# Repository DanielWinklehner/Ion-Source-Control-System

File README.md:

# Ion Source Control System

## Arduino Error Codes
'ERR0' => Undefined error (does not fall into any of the other 9 categories).
'ERR1' => Asking a precision that's too high (> 6).
'ERR2' => Asking for something that would return more than 128 bytes.
'ERR3' => Invalid number of channels.
'ERR4' => Querying for a channel that does not exist.
'ERR5' => ...
'ERR6' => ...
'ERR7' => ...
...

## Libraries to Install

## Killing the server.

```bash
ps aux | grep RasPiServer.py | grep -v grep | awk '{print $2}' | xargs kill -9 ; python RasPiServer.py 
```

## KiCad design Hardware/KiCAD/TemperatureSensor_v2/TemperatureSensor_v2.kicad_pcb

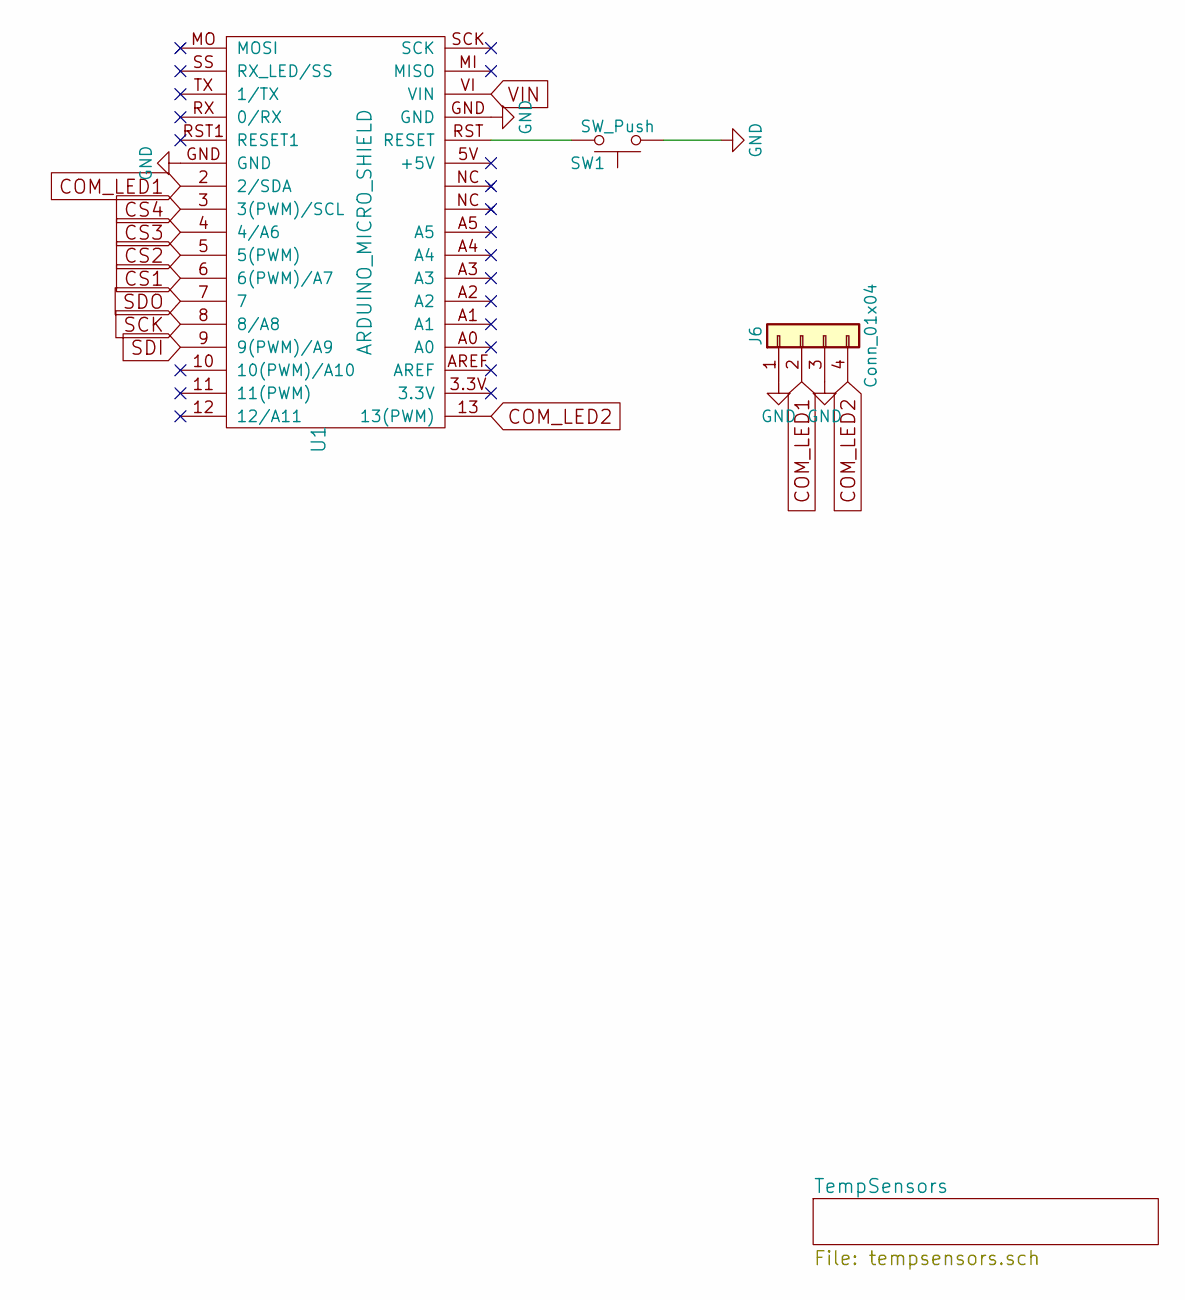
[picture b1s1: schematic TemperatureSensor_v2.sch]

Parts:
J6: Conn_01x04; TerminalBlock_Phoenix_MPT-2.54mm_4pol
SW1: SW_Push; SW_Tactile_SPST_Angled_PTS645Vx39-2LFS
U1: ARDUINO_MICRO_SHIELD; ARDUINO_MICRO_SHIELD1

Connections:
COM_LED1: J6.2, U1.2 (2/SDA)
COM_LED2: J6.4, U1.13 (13(PWM))
CS1: U1.6 (6(PWM)/A7); also elsewhere on the board
CS2: U1.5 (5(PWM)); also elsewhere on the board
CS3: U1.4 (4/A6); also elsewhere on the board
CS4: U1.3 (3(PWM)/SCL); also elsewhere on the board
GND: J6.1, J6.3, SW1.1, U1.GND; also elsewhere on the board
unnamed: SW1.2, U1.RST (RESET)
SCK: U1.8 (8/A8); also elsewhere on the board
SDI: U1.9 (9(PWM)/A9); also elsewhere on the board
SDO: U1.7; also elsewhere on the board
VIN: U1.VI (VIN); also elsewhere on the board

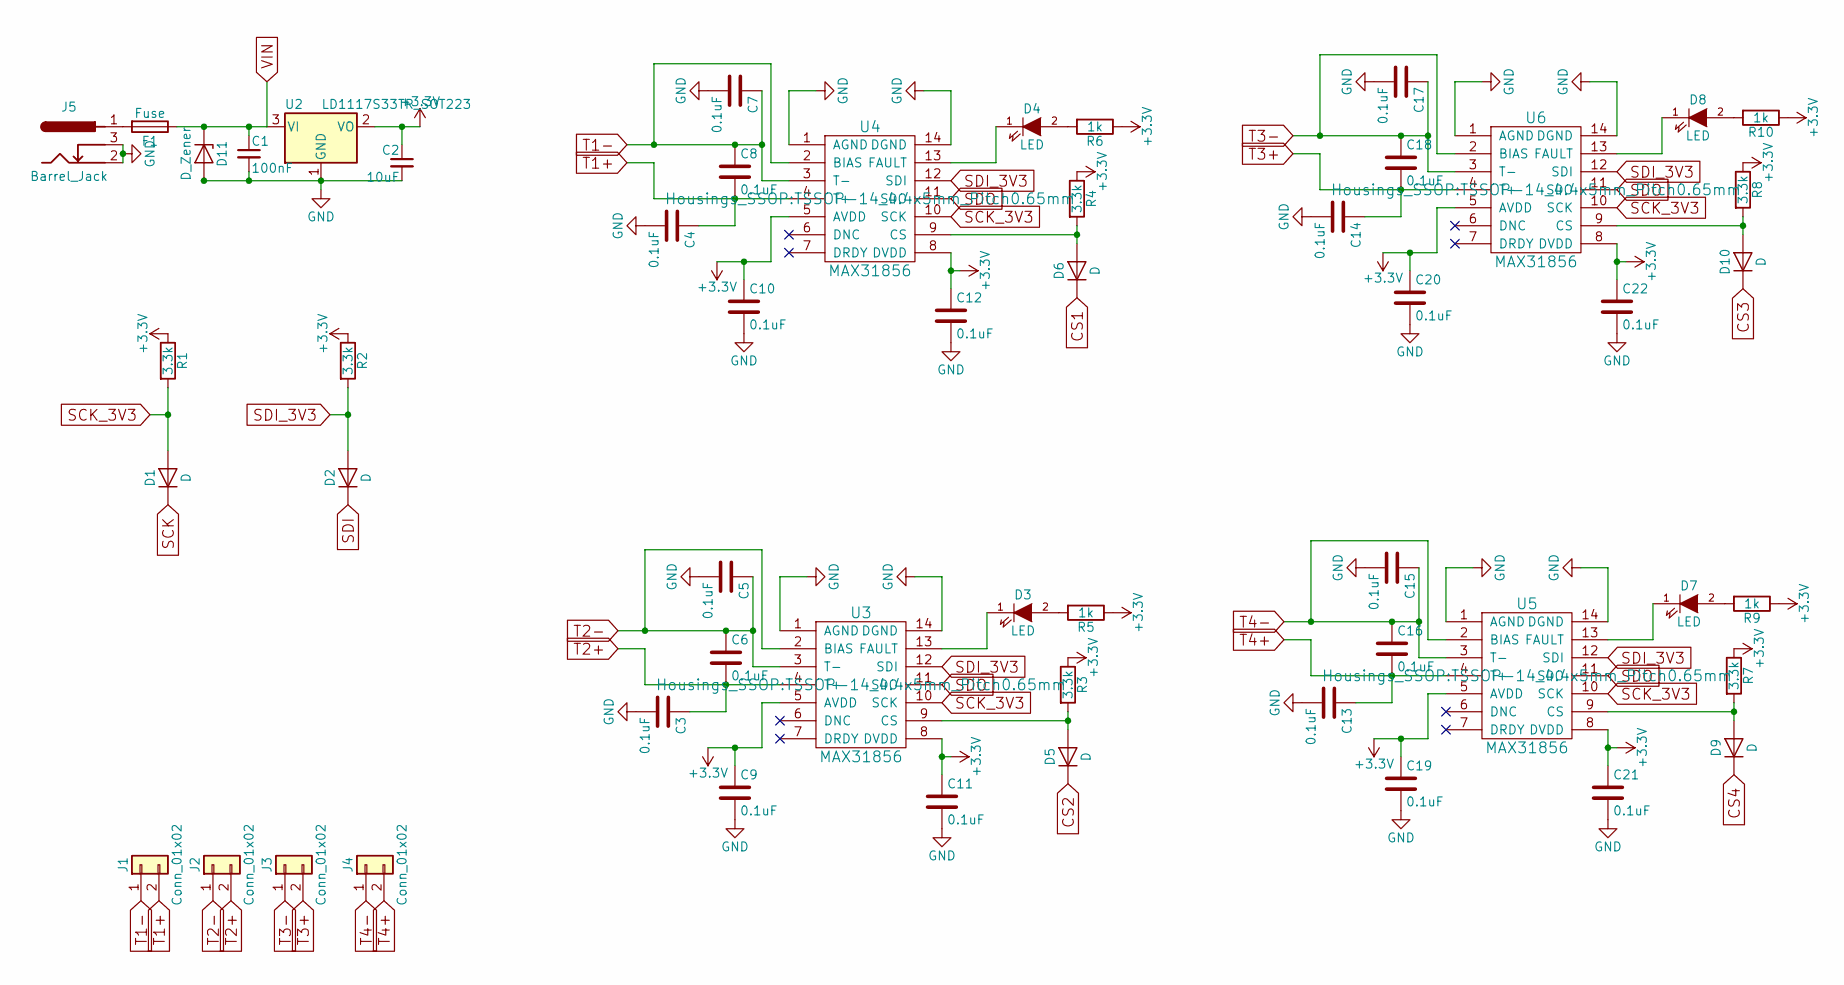
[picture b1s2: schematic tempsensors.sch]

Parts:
C1: 100nF; C_0805
C2: 10uF; C_0805
C3, C4, C5, C6, C7, C8, C9, C10, C11, C12, C13, C14, C15, C16, C17, C18, C19, C20, C21, C22: 0.1uF; C_0805
D1, D2, D5, D6, D9, D10: D; D_SOD-323
D3, D4, D7, D8: LED; LED_0603
D11: D_Zener; D_0805
F1: Fuse; Fuseholder5x20_horiz_open_inline_Type-I
J1, J2, J3, J4: Conn_01x02; Thermocouple_Pins
J5: Barrel_Jack; BARREL_JACK
R1, R2, R3, R4, R7, R8: 3.3k; R_0603
R5, R6, R9, R10: 1k; R_0603
U2: LD1117S33TR_SOT223; TO-220-3_Vertical
U3, U4, U5, U6: MAX31856; TSSOP-14_4.4x5mm_Pitch0.65mm

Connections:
+3V3: C2.1, C9.1, C10.1, C11.1, C12.1, C19.1, C20.1, C21.1, C22.1, R1.1, R2.1, R3.1, R4.1, R5.1, R6.1, R7.1, R8.1, R9.1, R10.1, U2.2 (VO), U3.5 (AVDD), U3.8 (DVDD), U4.5 (AVDD), U4.8 (DVDD), U5.5 (AVDD), U5.8 (DVDD), U6.5 (AVDD), U6.8 (DVDD)
CS1: D6.1 (K); also elsewhere on the board
CS2: D5.1 (K); also elsewhere on the board
CS3: D10.1 (K); also elsewhere on the board
CS4: D9.1 (K); also elsewhere on the board
GND: C1.2, C2.2, C3.2, C4.2, C5.2, C7.2, C9.2, C10.2, C11.2, C12.2, C13.2, C14.2, C15.2, C17.2, C19.2, C20.2, C21.2, C22.2, D11.2 (A), J5.2, J5.3, U2.1 (GND), U3.1 (AGND), U3.14 (DGND), U4.1 (AGND), U4.14 (DGND), U5.1 (AGND), U5.14 (DGND), U6.1 (AGND), U6.14 (DGND); also elsewhere on the board
unnamed: D3.1 (K), U3.13 (FAULT)
unnamed: D3.2 (A), R5.2
unnamed: D4.1 (K), U4.13 (FAULT)
unnamed: D4.2 (A), R6.2
unnamed: D5.2 (A), R3.2, U3.9 (CS)
unnamed: D6.2 (A), R4.2, U4.9 (CS)
unnamed: D7.1 (K), U5.13 (FAULT)
unnamed: D7.2 (A), R9.2
unnamed: D8.1 (K), U6.13 (FAULT)
unnamed: D8.2 (A), R10.2
unnamed: D9.2 (A), R7.2, U5.9 (CS)
unnamed: D10.2 (A), R8.2, U6.9 (CS)
unnamed: F1.2, J5.1
SCK: D1.1 (K); also elsewhere on the board
SCK_3V3: D1.2 (A), R1.2, U3.10 (SCK), U4.10 (SCK), U5.10 (SCK), U6.10 (SCK)
SDI: D2.1 (K); also elsewhere on the board
SDI_3V3: D2.2 (A), R2.2, U3.12 (SDI), U4.12 (SDI), U5.12 (SDI), U6.12 (SDI)
SDO: U3.11 (SDO), U4.11 (SDO), U5.11 (SDO), U6.11 (SDO); also elsewhere on the board
T1+: C4.1, C8.2, J1.2, U4.4 (T+)
T1-: C7.1, C8.1, J1.1, U4.2 (BIAS), U4.3 (T-)
T2+: C3.1, C6.2, J2.2, U3.4 (T+)
T2-: C5.1, C6.1, J2.1, U3.2 (BIAS), U3.3 (T-)
T3+: C14.1, C18.2, J3.2, U6.4 (T+)
T3-: C17.1, C18.1, J3.1, U6.2 (BIAS), U6.3 (T-)
T4+: C13.1, C16.2, J4.2, U5.4 (T+)
T4-: C15.1, C16.1, J4.1, U5.2 (BIAS), U5.3 (T-)
VIN: C1.1, D11.1 (K), F1.1, U2.3 (VI); also elsewhere on the board

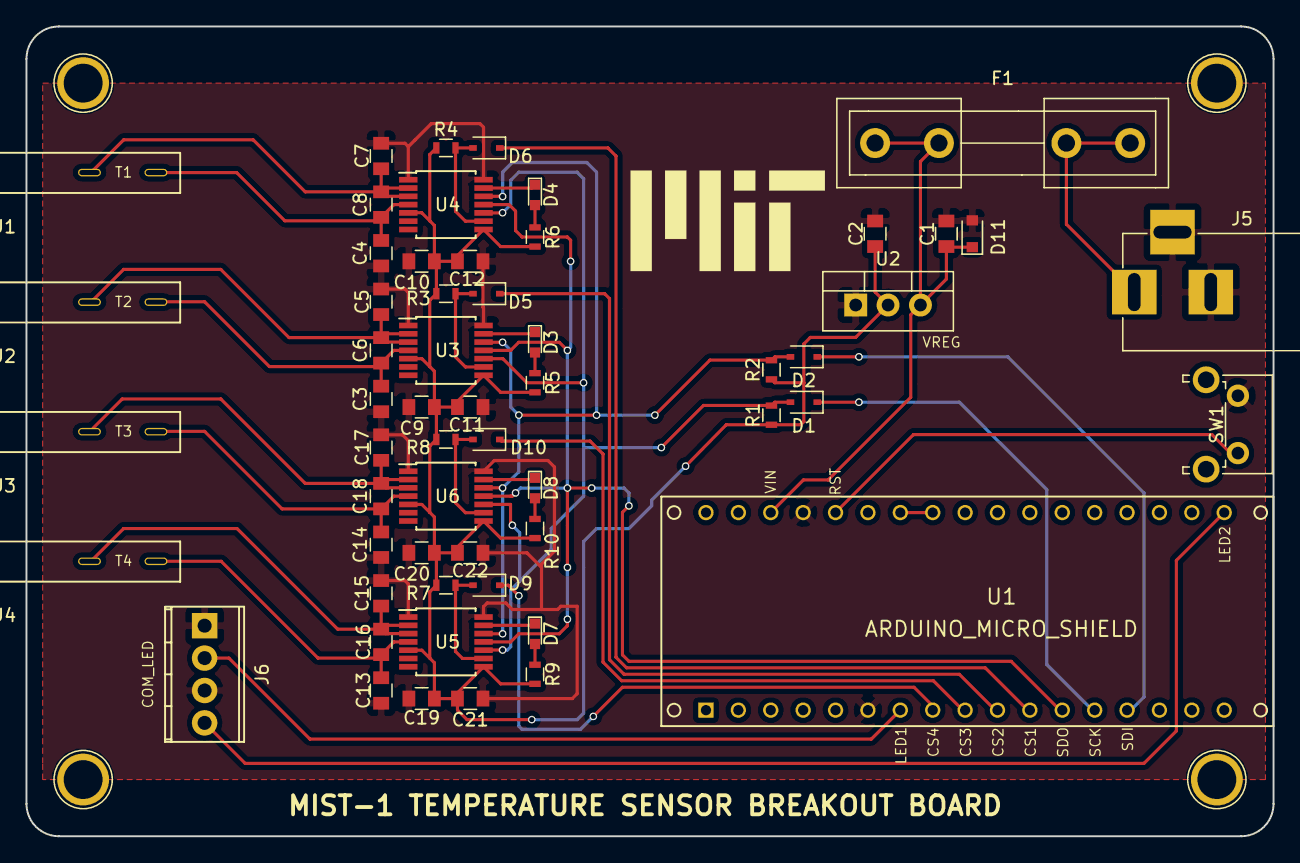
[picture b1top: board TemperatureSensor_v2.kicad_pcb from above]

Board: 2 copper layers, 97.8 x 63.5 mm, 57 parts (0 on the bottom side), 36 nets.

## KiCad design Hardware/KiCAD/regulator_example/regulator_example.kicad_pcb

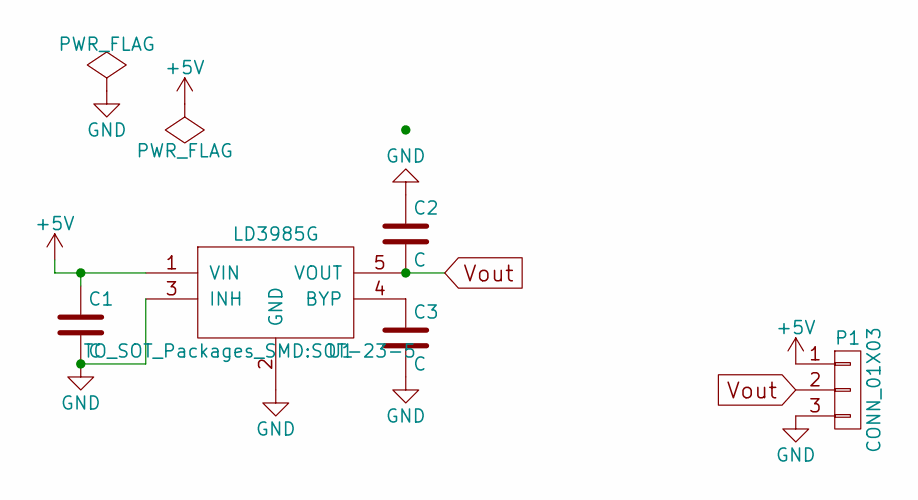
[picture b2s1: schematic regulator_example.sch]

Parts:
C1, C2, C3: C; C_0805_HandSoldering
P1: CONN_01X03; Pin_Header_Straight_1x03
U1: LD3985G; SOT-23-5

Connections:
+5V: C1.1, P1.1, U1.1 (VIN)
GND: C1.2, C2.1, C3.2, P1.3, U1.2 (GND), U1.3 (INH)
unnamed: C3.1, U1.4 (BYP)
Vout: C2.2, P1.2, U1.5 (VOUT)

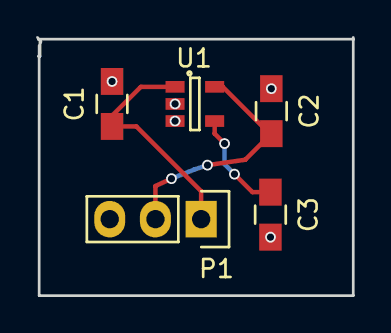
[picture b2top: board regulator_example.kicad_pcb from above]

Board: 2 copper layers, 17.6 x 14.4 mm, 5 parts (0 on the bottom side), 4 nets.

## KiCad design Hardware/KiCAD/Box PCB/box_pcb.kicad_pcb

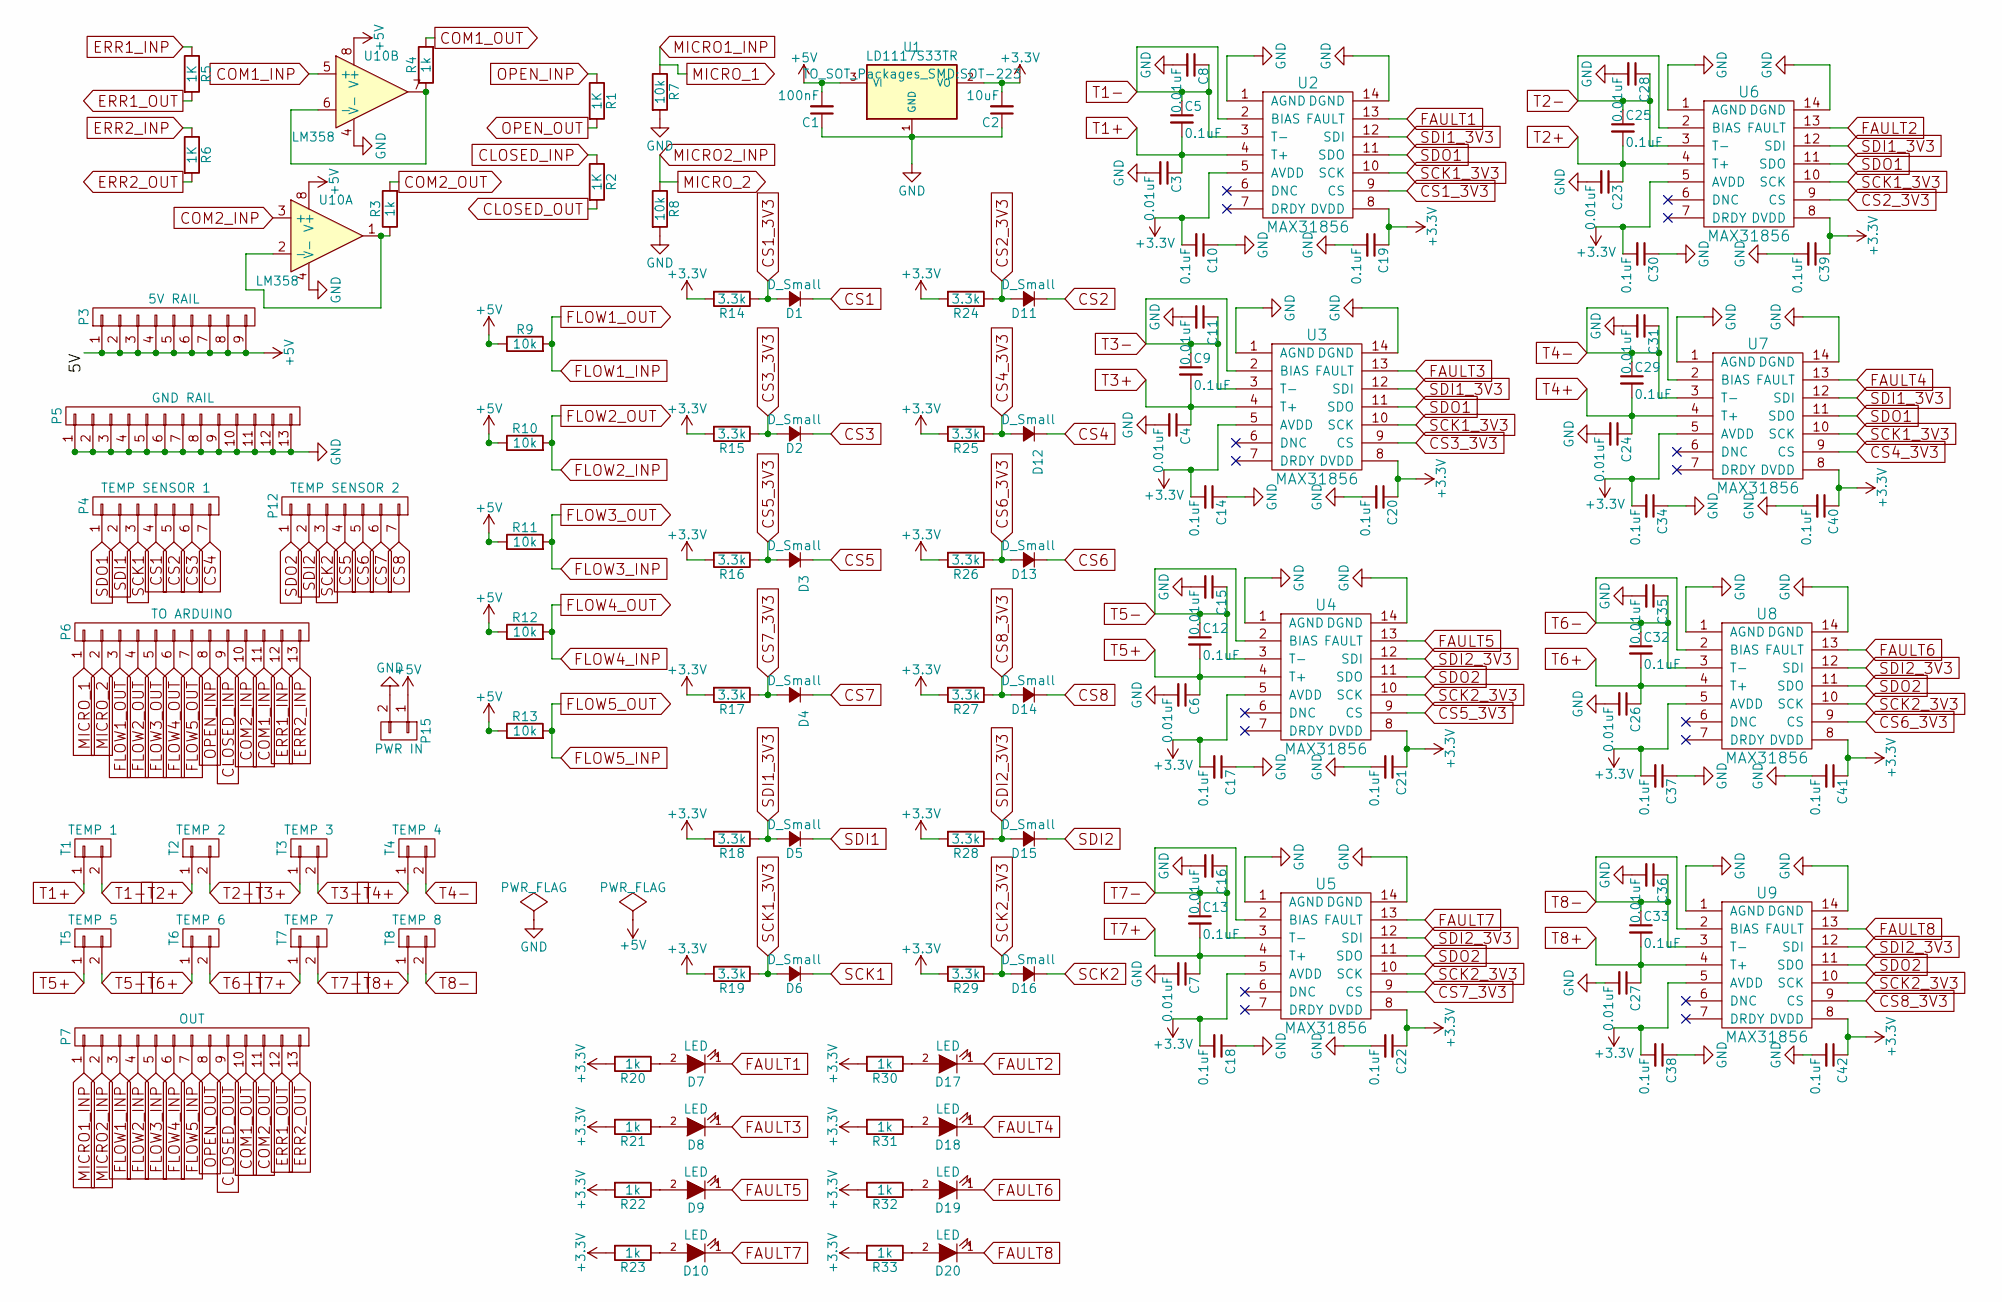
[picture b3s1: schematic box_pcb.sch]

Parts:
C1: 100nF; C_0805_HandSoldering
C2: 10uF; C_0805_HandSoldering
C3, C4, C6, C7, C8, C11, C15, C16, C23, C24, C26, C27, C28, C31, C35, C36: 0.01uF; C_0805_HandSoldering
C5, C9, C10, C12, C13, C14, C17, C18, C19, C20, C21, C22, C25, C29, C30, C32, C33, C34, C37, C38, C39, C40, C41, C42: 0.1uF; C_0805_HandSoldering
D1, D2, D3, D4, D5, D6, D11, D12, D13, D14, D15, D16: D_Small; SOD-323
D7, D8, D9, D10, D17, D18, D19, D20: LED; LED-3MM
P3: 5V RAIL; Socket_Strip_Straight_1x09
P4: TEMP SENSOR 1; Socket_Strip_Straight_1x07
P5: GND RAIL; Socket_Strip_Straight_1x13
P6: TO ARDUINO; Socket_Strip_Straight_1x13
P7: OUT; Socket_Strip_Straight_1x13
P12: TEMP SENSOR 2; Socket_Strip_Straight_1x07
P15: PWR IN; Socket_Strip_Straight_1x02
R1, R2, R5, R6: 1K; R_0603_HandSoldering
R3, R4, R20, R21, R22, R23, R30, R31, R32, R33: 1k; R_0603_HandSoldering
R7, R8, R9, R10, R11, R12, R13: 10k; R_0603_HandSoldering
R14, R15, R16, R17, R18, R19, R24, R25, R26, R27, R28, R29: 3.3k; R_0603_HandSoldering
T1: TEMP 1; Socket_Strip_Straight_1x02
T2: TEMP 2; Socket_Strip_Straight_1x02
T3: TEMP 3; Socket_Strip_Straight_1x02
T4: TEMP 4; Socket_Strip_Straight_1x02
T5: TEMP 5; Socket_Strip_Straight_1x02
T6: TEMP 6; Socket_Strip_Straight_1x02
T7: TEMP 7; Socket_Strip_Straight_1x02
T8: TEMP 8; Socket_Strip_Straight_1x02
U1: LD1117S33TR; SOT-223
U2, U3, U4, U5, U6, U7, U8, U9: MAX31856; TSSOP-14_4.4x5mm_Pitch0.65mm
U10: LM358; SOIC-8-N

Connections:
+3V3: C2.2, C10.2, C14.2, C17.2, C18.2, C19.1, C20.1, C21.1, C22.1, C30.2, C34.2, C37.2, C38.2, C39.1, C40.1, C41.1, C42.1, R14.2, R15.2, R16.2, R17.2, R18.2, R19.2, R20.2, R21.2, R22.2, R23.2, R24.2, R25.2, R26.2, R27.2, R28.2, R29.2, R30.2, R31.2, R32.2, R33.2, U1.2 (VO), U2.5 (AVDD), U2.8 (DVDD), U3.5 (AVDD), U3.8 (DVDD), U4.5 (AVDD), U4.8 (DVDD), U5.5 (AVDD), U5.8 (DVDD), U6.5 (AVDD), U6.8 (DVDD), U7.5 (AVDD), U7.8 (DVDD), U8.5 (AVDD), U8.8 (DVDD), U9.5 (AVDD), U9.8 (DVDD)
+5V: C1.2, P3.1, P3.2, P3.3, P3.4, P3.5, P3.6, P3.7, P3.8, P3.9, P15.1, R9.1, R10.1, R11.1, R12.1, R13.1, U1.3 (VI), U10.8 (V+)
CLOSED_INP: P6.9, R2.1
CLOSED_OUT: P7.9, R2.2
COM1_INP: P6.11, U10.5 (+)
COM1_OUT: P7.10, R4.2
COM2_INP: P6.10, U10.3 (+)
COM2_OUT: P7.11, R3.2
CS1: D1.1 (K), P4.4
CS1_3V3: D1.2 (A), R14.1, U2.9 (CS)
CS2: D11.1 (K), P4.5
CS2_3V3: D11.2 (A), R24.1, U6.9 (CS)
CS3: D2.1 (K), P4.6
CS3_3V3: D2.2 (A), R15.1, U3.9 (CS)
CS4: D12.1 (K), P4.7
CS4_3V3: D12.2 (A), R25.1, U7.9 (CS)
CS5: D3.1 (K), P12.4
CS5_3V3: D3.2 (A), R16.1, U4.9 (CS)
CS6: D13.1 (K), P12.5
CS6_3V3: D13.2 (A), R26.1, U8.9 (CS)
CS7: D4.1 (K), P12.6
CS7_3V3: D4.2 (A), R17.1, U5.9 (CS)
CS8: D14.1 (K), P12.7
CS8_3V3: D14.2 (A), R27.1, U9.9 (CS)
ERR1_INP: P6.12, R5.1
ERR1_OUT: P7.12, R5.2
ERR2_INP: P6.13, R6.1
ERR2_OUT: P7.13, R6.2
FAULT1: D7.1 (K), U2.13 (FAULT)
FAULT2: D17.1 (K), U6.13 (FAULT)
FAULT3: D8.1 (K), U3.13 (FAULT)
FAULT4: D18.1 (K), U7.13 (FAULT)
FAULT5: D9.1 (K), U4.13 (FAULT)
FAULT6: D19.1 (K), U8.13 (FAULT)
FAULT7: D10.1 (K), U5.13 (FAULT)
FAULT8: D20.1 (K), U9.13 (FAULT)
FLOW1_INP: P6.3, P7.3, R9.2
FLOW2_INP: P6.4, P7.4, R10.2
FLOW3_INP: P6.5, P7.5, R11.2
FLOW4_INP: P6.6, P7.6, R12.2
FLOW5_INP: P6.7, P7.7, R13.2
GND: C1.1, C2.1, C3.2, C4.2, C6.2, C7.2, C8.2, C10.1, C11.2, C14.1, C15.2, C16.2, C17.1, C18.1, C19.2, C20.2, C21.2, C22.2, C23.2, C24.2, C26.2, C27.2, C28.2, C30.1, C31.2, C34.1, C35.2, C36.2, C37.1, C38.1, C39.2, C40.2, C41.2, C42.2, P5.1, P5.2, P5.3, P5.4, P5.5, P5.6, P5.7, P5.8, P5.9, P5.10, P5.11, P5.12, P5.13, P15.2, R7.2, R8.2, U1.1 (GND), U2.1 (AGND), U2.14 (DGND), U3.1 (AGND), U3.14 (DGND), U4.1 (AGND), U4.14 (DGND), U5.1 (AGND), U5.14 (DGND), U6.1 (AGND), U6.14 (DGND), U7.1 (AGND), U7.14 (DGND), U8.1 (AGND), U8.14 (DGND), U9.1 (AGND), U9.14 (DGND), U10.4 (V-)
MICRO1_INP: P6.1, P7.1, R7.1
MICRO2_INP: P6.2, P7.2, R8.1
unnamed: D7.2 (A), R20.1
unnamed: D8.2 (A), R21.1
unnamed: D9.2 (A), R22.1
unnamed: D10.2 (A), R23.1
unnamed: D17.2 (A), R30.1
unnamed: D18.2 (A), R31.1
unnamed: D19.2 (A), R32.1
unnamed: D20.2 (A), R33.1
unnamed: R3.1, U10.1, U10.2 (-)
unnamed: R4.1, U10.6 (-), U10.7
OPEN_INP: P6.8, R1.1
OPEN_OUT: P7.8, R1.2
SCK1: D6.1 (K), P4.3
SCK1_3V3: D6.2 (A), R19.1, U2.10 (SCK), U3.10 (SCK), U6.10 (SCK), U7.10 (SCK)
SCK2: D16.1 (K), P12.3
SCK2_3V3: D16.2 (A), R29.1, U4.10 (SCK), U5.10 (SCK), U8.10 (SCK), U9.10 (SCK)
SDI1: D5.1 (K), P4.2
SDI1_3V3: D5.2 (A), R18.1, U2.12 (SDI), U3.12 (SDI), U6.12 (SDI), U7.12 (SDI)
SDI2: D15.1 (K), P12.2
SDI2_3V3: D15.2 (A), R28.1, U4.12 (SDI), U5.12 (SDI), U8.12 (SDI), U9.12 (SDI)
SDO1: P4.1, U2.11 (SDO), U3.11 (SDO), U6.11 (SDO), U7.11 (SDO)
SDO2: P12.1, U4.11 (SDO), U5.11 (SDO), U8.11 (SDO), U9.11 (SDO)
T1+: C3.1, C5.2, T1.1, U2.4 (T+)
T1-: C5.1, C8.1, T1.2, U2.2 (BIAS), U2.3 (T-)
T2+: C23.1, C25.2, T2.1, U6.4 (T+)
T2-: C25.1, C28.1, T2.2, U6.2 (BIAS), U6.3 (T-)
T3+: C4.1, C9.2, T3.1, U3.4 (T+)
T3-: C9.1, C11.1, T3.2, U3.2 (BIAS), U3.3 (T-)
T4+: C24.1, C29.2, T4.1, U7.4 (T+)
T4-: C29.1, C31.1, T4.2, U7.2 (BIAS), U7.3 (T-)
T5+: C6.1, C12.2, T5.1, U4.4 (T+)
T5-: C12.1, C15.1, T5.2, U4.2 (BIAS), U4.3 (T-)
T6+: C26.1, C32.2, T6.1, U8.4 (T+)
T6-: C32.1, C35.1, T6.2, U8.2 (BIAS), U8.3 (T-)
T7+: C7.1, C13.2, T7.1, U5.4 (T+)
T7-: C13.1, C16.1, T7.2, U5.2 (BIAS), U5.3 (T-)
T8+: C27.1, C33.2, T8.1, U9.4 (T+)
T8-: C33.1, C36.1, T8.2, U9.2 (BIAS), U9.3 (T-)

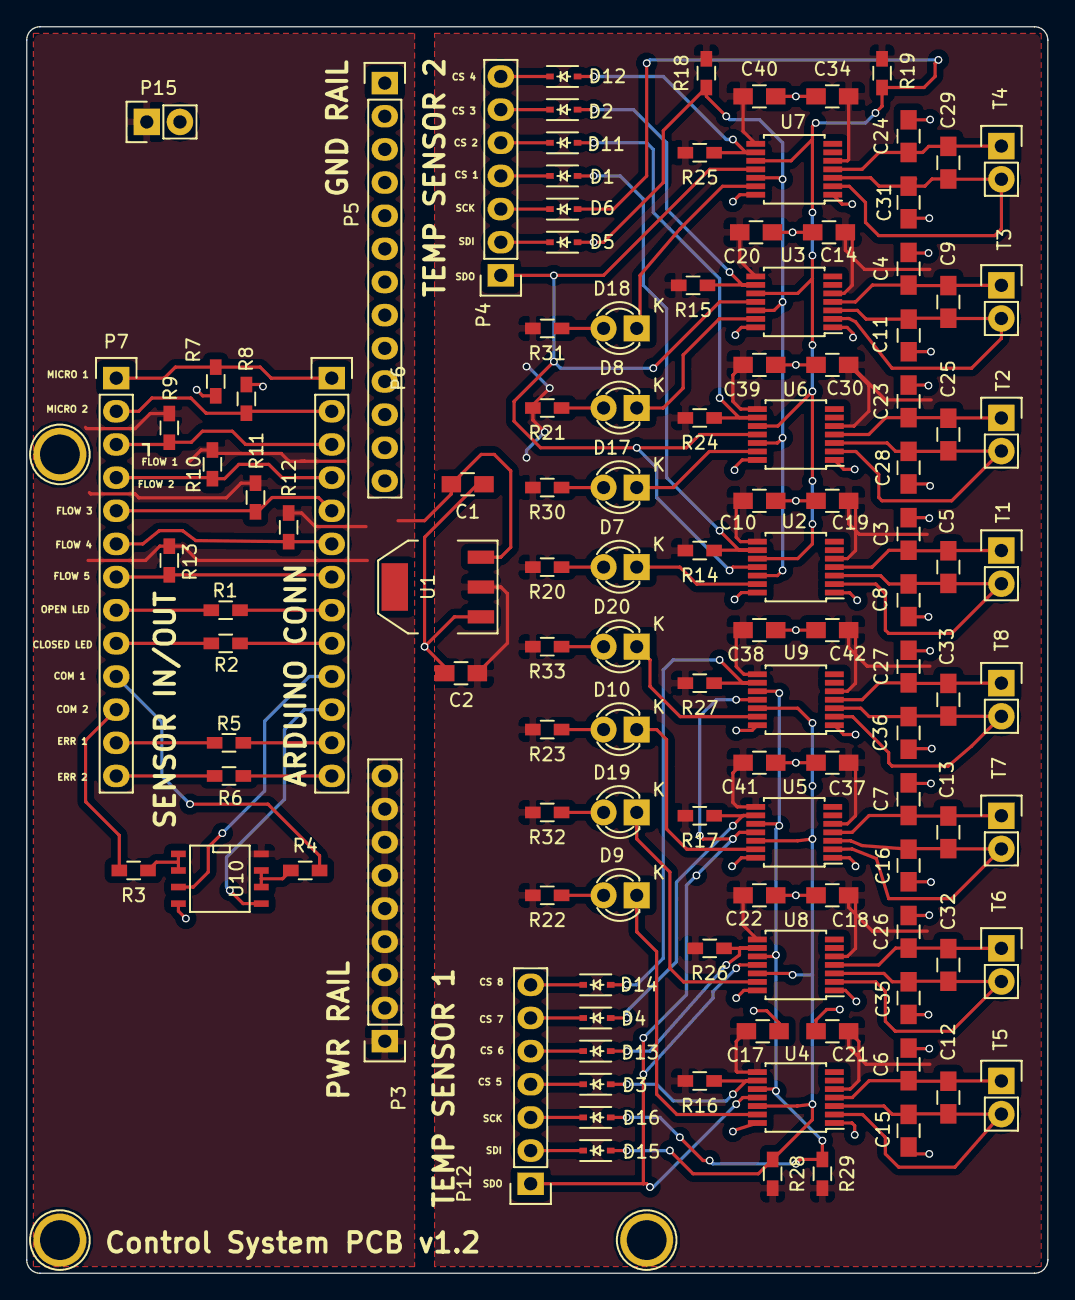
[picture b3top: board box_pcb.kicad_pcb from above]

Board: 2 copper layers, 78.2 x 95.5 mm, 120 parts (0 on the bottom side), 82 nets.

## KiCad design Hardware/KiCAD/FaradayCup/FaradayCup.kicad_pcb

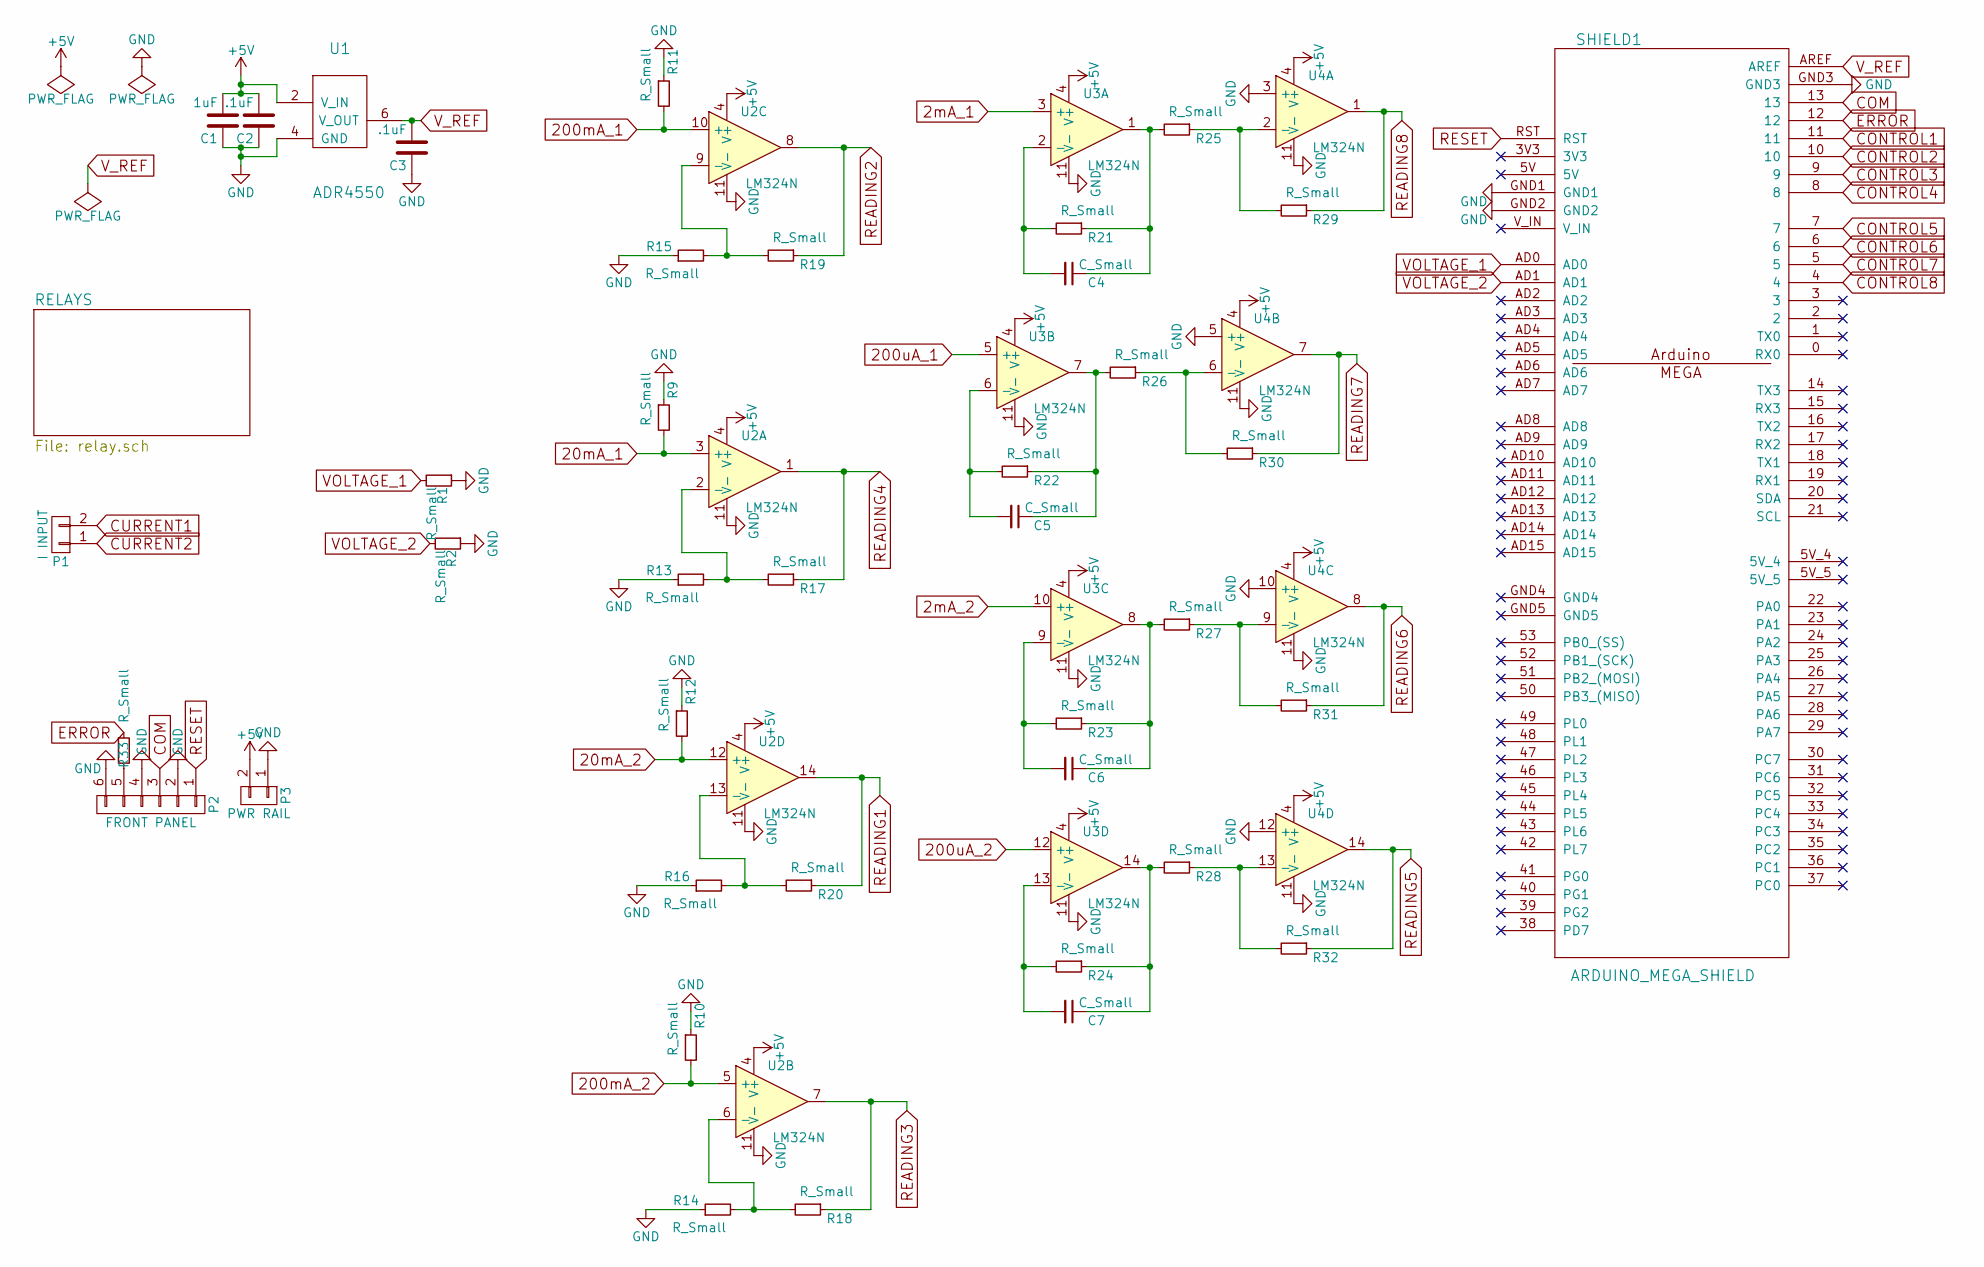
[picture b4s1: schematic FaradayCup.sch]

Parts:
C1: 1uF; C_0805
C2, C3: .1uF; C_0805
C4, C5, C6, C7: C_Small; C_0805
P1: I INPUT; TerminalBlock_Pheonix_PT-3.5mm_2pol
P2: FRONT PANEL; Pin_Header_Straight_1x06
P3: PWR RAIL; Pin_Header_Straight_1x02
R1, R2, R9, R10, R11, R12, R13, R14, R15, R16, R17, R18, R19, R20, R21, R22, R23, R24, R25, R26, R27, R28, R29, R30, R31, R32, R33: R_Small; R_0603
SHIELD1: ARDUINO_MEGA_SHIELD
U1: ADR4550; SOIC-8_3.9x4.9mm_Pitch1.27mm
U2, U3, U4: LM324N; SOIC-14_3.9x8.7mm_Pitch1.27mm

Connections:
2mA_1: U3.3 (+); also elsewhere on the board
2mA_2: U3.10 (+); also elsewhere on the board
20mA_1: R9.2, U2.3 (+); also elsewhere on the board
20mA_2: R12.2, U2.12 (+); also elsewhere on the board
200mA_1: R11.2, U2.10 (+); also elsewhere on the board
200mA_2: R10.2, U2.5 (+); also elsewhere on the board
200uA_1: U3.5 (+); also elsewhere on the board
200uA_2: U3.12 (+); also elsewhere on the board
+5V: C1.2, C2.2, P3.2, U1.2 (V_IN), U2.4 (V+), U3.4 (V+), U4.4 (V+); also elsewhere on the board
COM: P2.3, SHIELD1.13
CONTROL1: SHIELD1.11; also elsewhere on the board
CONTROL2: SHIELD1.10; also elsewhere on the board
CONTROL3: SHIELD1.9; also elsewhere on the board
CONTROL4: SHIELD1.8; also elsewhere on the board
CONTROL5: SHIELD1.7; also elsewhere on the board
CONTROL6: SHIELD1.6; also elsewhere on the board
CONTROL7: SHIELD1.5; also elsewhere on the board
CONTROL8: SHIELD1.4; also elsewhere on the board
CURRENT1: P1.2; also elsewhere on the board
CURRENT2: P1.1; also elsewhere on the board
ERROR: R33.1, SHIELD1.12
GND: C1.1, C2.1, C3.1, P2.2, P2.4, P2.6, P3.1, R1.1, R2.1, R9.1, R10.1, R11.1, R12.1, R13.1, R14.1, R15.1, R16.1, SHIELD1.GND1, SHIELD1.GND2, SHIELD1.GND3, U1.4 (GND), U2.11 (V-), U3.11 (V-), U4.3 (+), U4.5 (+), U4.10 (+), U4.11 (V-), U4.12 (+); also elsewhere on the board
unnamed: C4.1, R21.1, R25.2, U3.1
unnamed: C4.2, R21.2, U3.2 (-)
unnamed: C5.1, R22.1, R26.2, U3.7
unnamed: C5.2, R22.2, U3.6 (-)
unnamed: C6.1, R23.1, R27.2, U3.8
unnamed: C6.2, R23.2, U3.9 (-)
unnamed: C7.1, R24.1, R28.2, U3.14
unnamed: C7.2, R24.2, U3.13 (-)
unnamed: P2.5, R33.2
unnamed: R13.2, R17.2, U2.2 (-)
unnamed: R14.2, R18.2, U2.6 (-)
unnamed: R15.2, R19.2, U2.9 (-)
unnamed: R16.2, R20.2, U2.13 (-)
unnamed: R25.1, R29.2, U4.2 (-)
unnamed: R26.1, R30.2, U4.6 (-)
unnamed: R27.1, R31.2, U4.9 (-)
unnamed: R28.1, R32.2, U4.13 (-)
READING1: R20.1, U2.14; also elsewhere on the board
READING2: R19.1, U2.8; also elsewhere on the board
READING3: R18.1, U2.7; also elsewhere on the board
READING4: R17.1, U2.1; also elsewhere on the board
READING5: R32.1, U4.14; also elsewhere on the board
READING6: R31.1, U4.8; also elsewhere on the board
READING7: R30.1, U4.7; also elsewhere on the board
READING8: R29.1, U4.1; also elsewhere on the board
RESET: P2.1, SHIELD1.RST
VOLTAGE_1: R1.2, SHIELD1.AD0; also elsewhere on the board
VOLTAGE_2: R2.2, SHIELD1.AD1; also elsewhere on the board
V_REF: C3.2, SHIELD1.AREF, U1.6 (V_OUT)

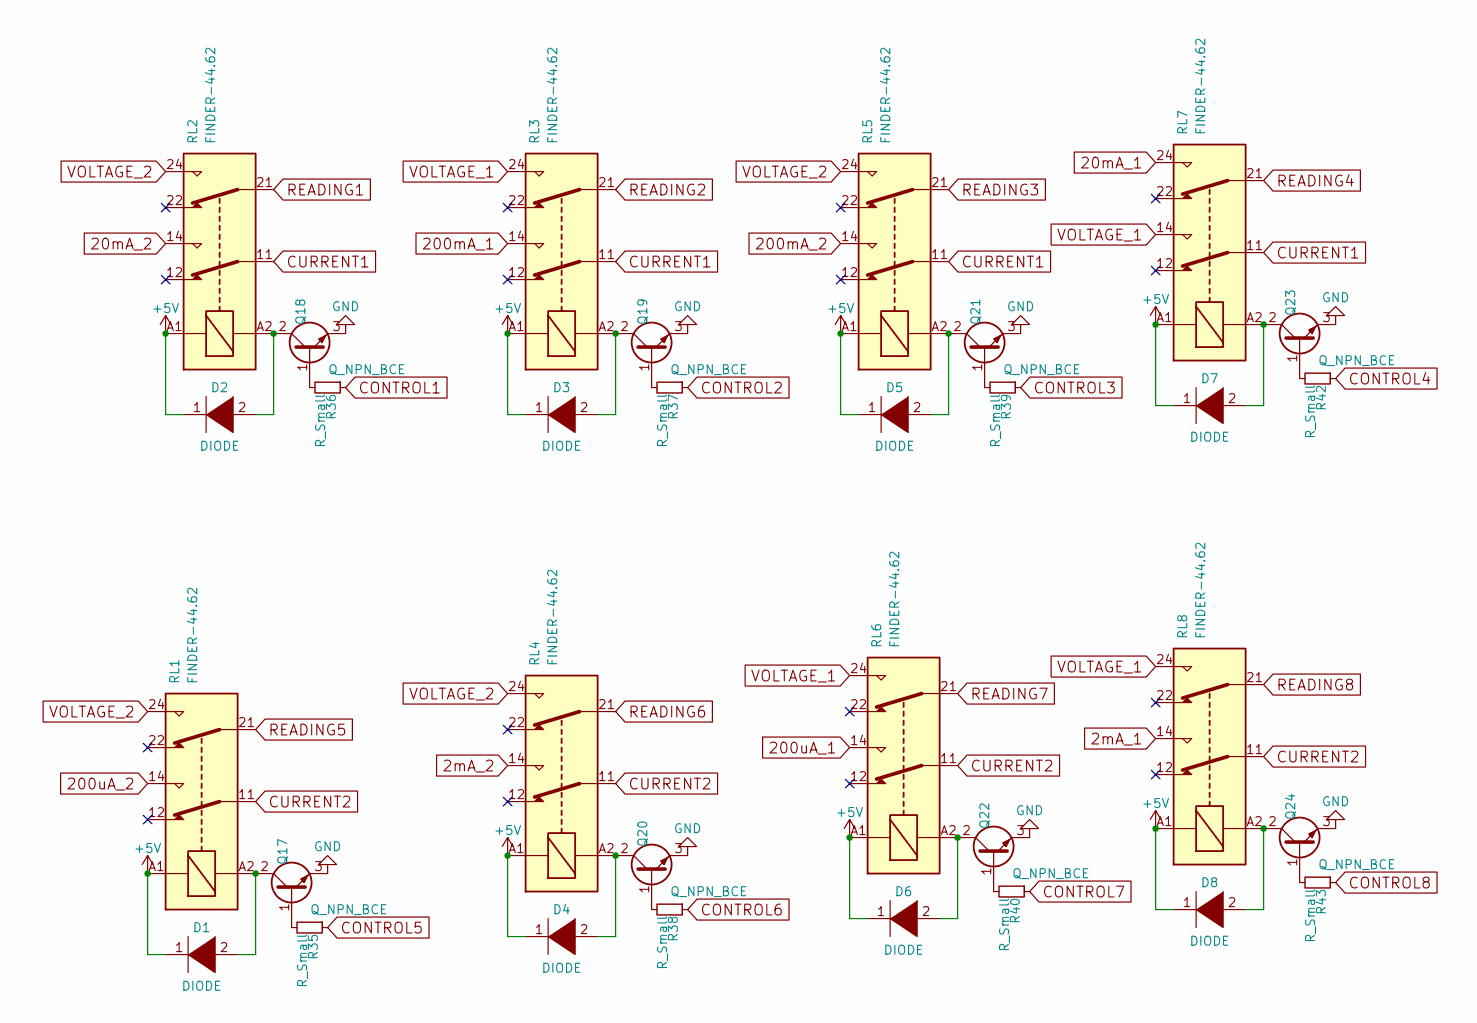
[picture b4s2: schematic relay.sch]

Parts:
D1, D2, D3, D4, D5, D6, D7, D8: DIODE; SOD-123
Q17, Q18, Q19, Q20, Q21, Q22, Q23, Q24: Q_NPN_BCE; TO-92_Inline_Wide
R35, R36, R37, R38, R39, R40, R42, R43: R_Small; R_0603
RL1, RL2, RL3, RL4, RL5, RL6, RL7, RL8: FINDER-44.62; RELAY

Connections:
2mA_1: RL8.14; also elsewhere on the board
2mA_2: RL4.14; also elsewhere on the board
20mA_1: RL7.24; also elsewhere on the board
20mA_2: RL2.14; also elsewhere on the board
200mA_1: RL3.14; also elsewhere on the board
200mA_2: RL5.14; also elsewhere on the board
200uA_1: RL6.14; also elsewhere on the board
200uA_2: RL1.14; also elsewhere on the board
+5V: D1.1 (K), D2.1 (K), D3.1 (K), D4.1 (K), D5.1 (K), D6.1 (K), D7.1 (K), D8.1 (K), RL1.A1, RL2.A1, RL3.A1, RL4.A1, RL5.A1, RL6.A1, RL7.A1, RL8.A1; also elsewhere on the board
CONTROL1: R36.1; also elsewhere on the board
CONTROL2: R37.1; also elsewhere on the board
CONTROL3: R39.1; also elsewhere on the board
CONTROL4: R42.1; also elsewhere on the board
CONTROL5: R35.1; also elsewhere on the board
CONTROL6: R38.1; also elsewhere on the board
CONTROL7: R40.1; also elsewhere on the board
CONTROL8: R43.1; also elsewhere on the board
CURRENT1: RL2.11, RL3.11, RL5.11, RL7.11; also elsewhere on the board
CURRENT2: RL1.11, RL4.11, RL6.11, RL8.11; also elsewhere on the board
GND: Q17.3 (E), Q18.3 (E), Q19.3 (E), Q20.3 (E), Q21.3 (E), Q22.3 (E), Q23.3 (E), Q24.3 (E); also elsewhere on the board
unnamed: D1.2 (A), Q17.2 (C), RL1.A2
unnamed: D2.2 (A), Q18.2 (C), RL2.A2
unnamed: D3.2 (A), Q19.2 (C), RL3.A2
unnamed: D4.2 (A), Q20.2 (C), RL4.A2
unnamed: D5.2 (A), Q21.2 (C), RL5.A2
unnamed: D6.2 (A), Q22.2 (C), RL6.A2
unnamed: D7.2 (A), Q23.2 (C), RL7.A2
unnamed: D8.2 (A), Q24.2 (C), RL8.A2
unnamed: Q17.1 (B), R35.2
unnamed: Q18.1 (B), R36.2
unnamed: Q19.1 (B), R37.2
unnamed: Q20.1 (B), R38.2
unnamed: Q21.1 (B), R39.2
unnamed: Q22.1 (B), R40.2
unnamed: Q23.1 (B), R42.2
unnamed: Q24.1 (B), R43.2
READING1: RL2.21; also elsewhere on the board
READING2: RL3.21; also elsewhere on the board
READING3: RL5.21; also elsewhere on the board
READING4: RL7.21; also elsewhere on the board
READING5: RL1.21; also elsewhere on the board
READING6: RL4.21; also elsewhere on the board
READING7: RL6.21; also elsewhere on the board
READING8: RL8.21; also elsewhere on the board
VOLTAGE_1: RL3.24, RL6.24, RL7.14, RL8.24; also elsewhere on the board
VOLTAGE_2: RL1.24, RL2.24, RL4.24, RL5.24; also elsewhere on the board
